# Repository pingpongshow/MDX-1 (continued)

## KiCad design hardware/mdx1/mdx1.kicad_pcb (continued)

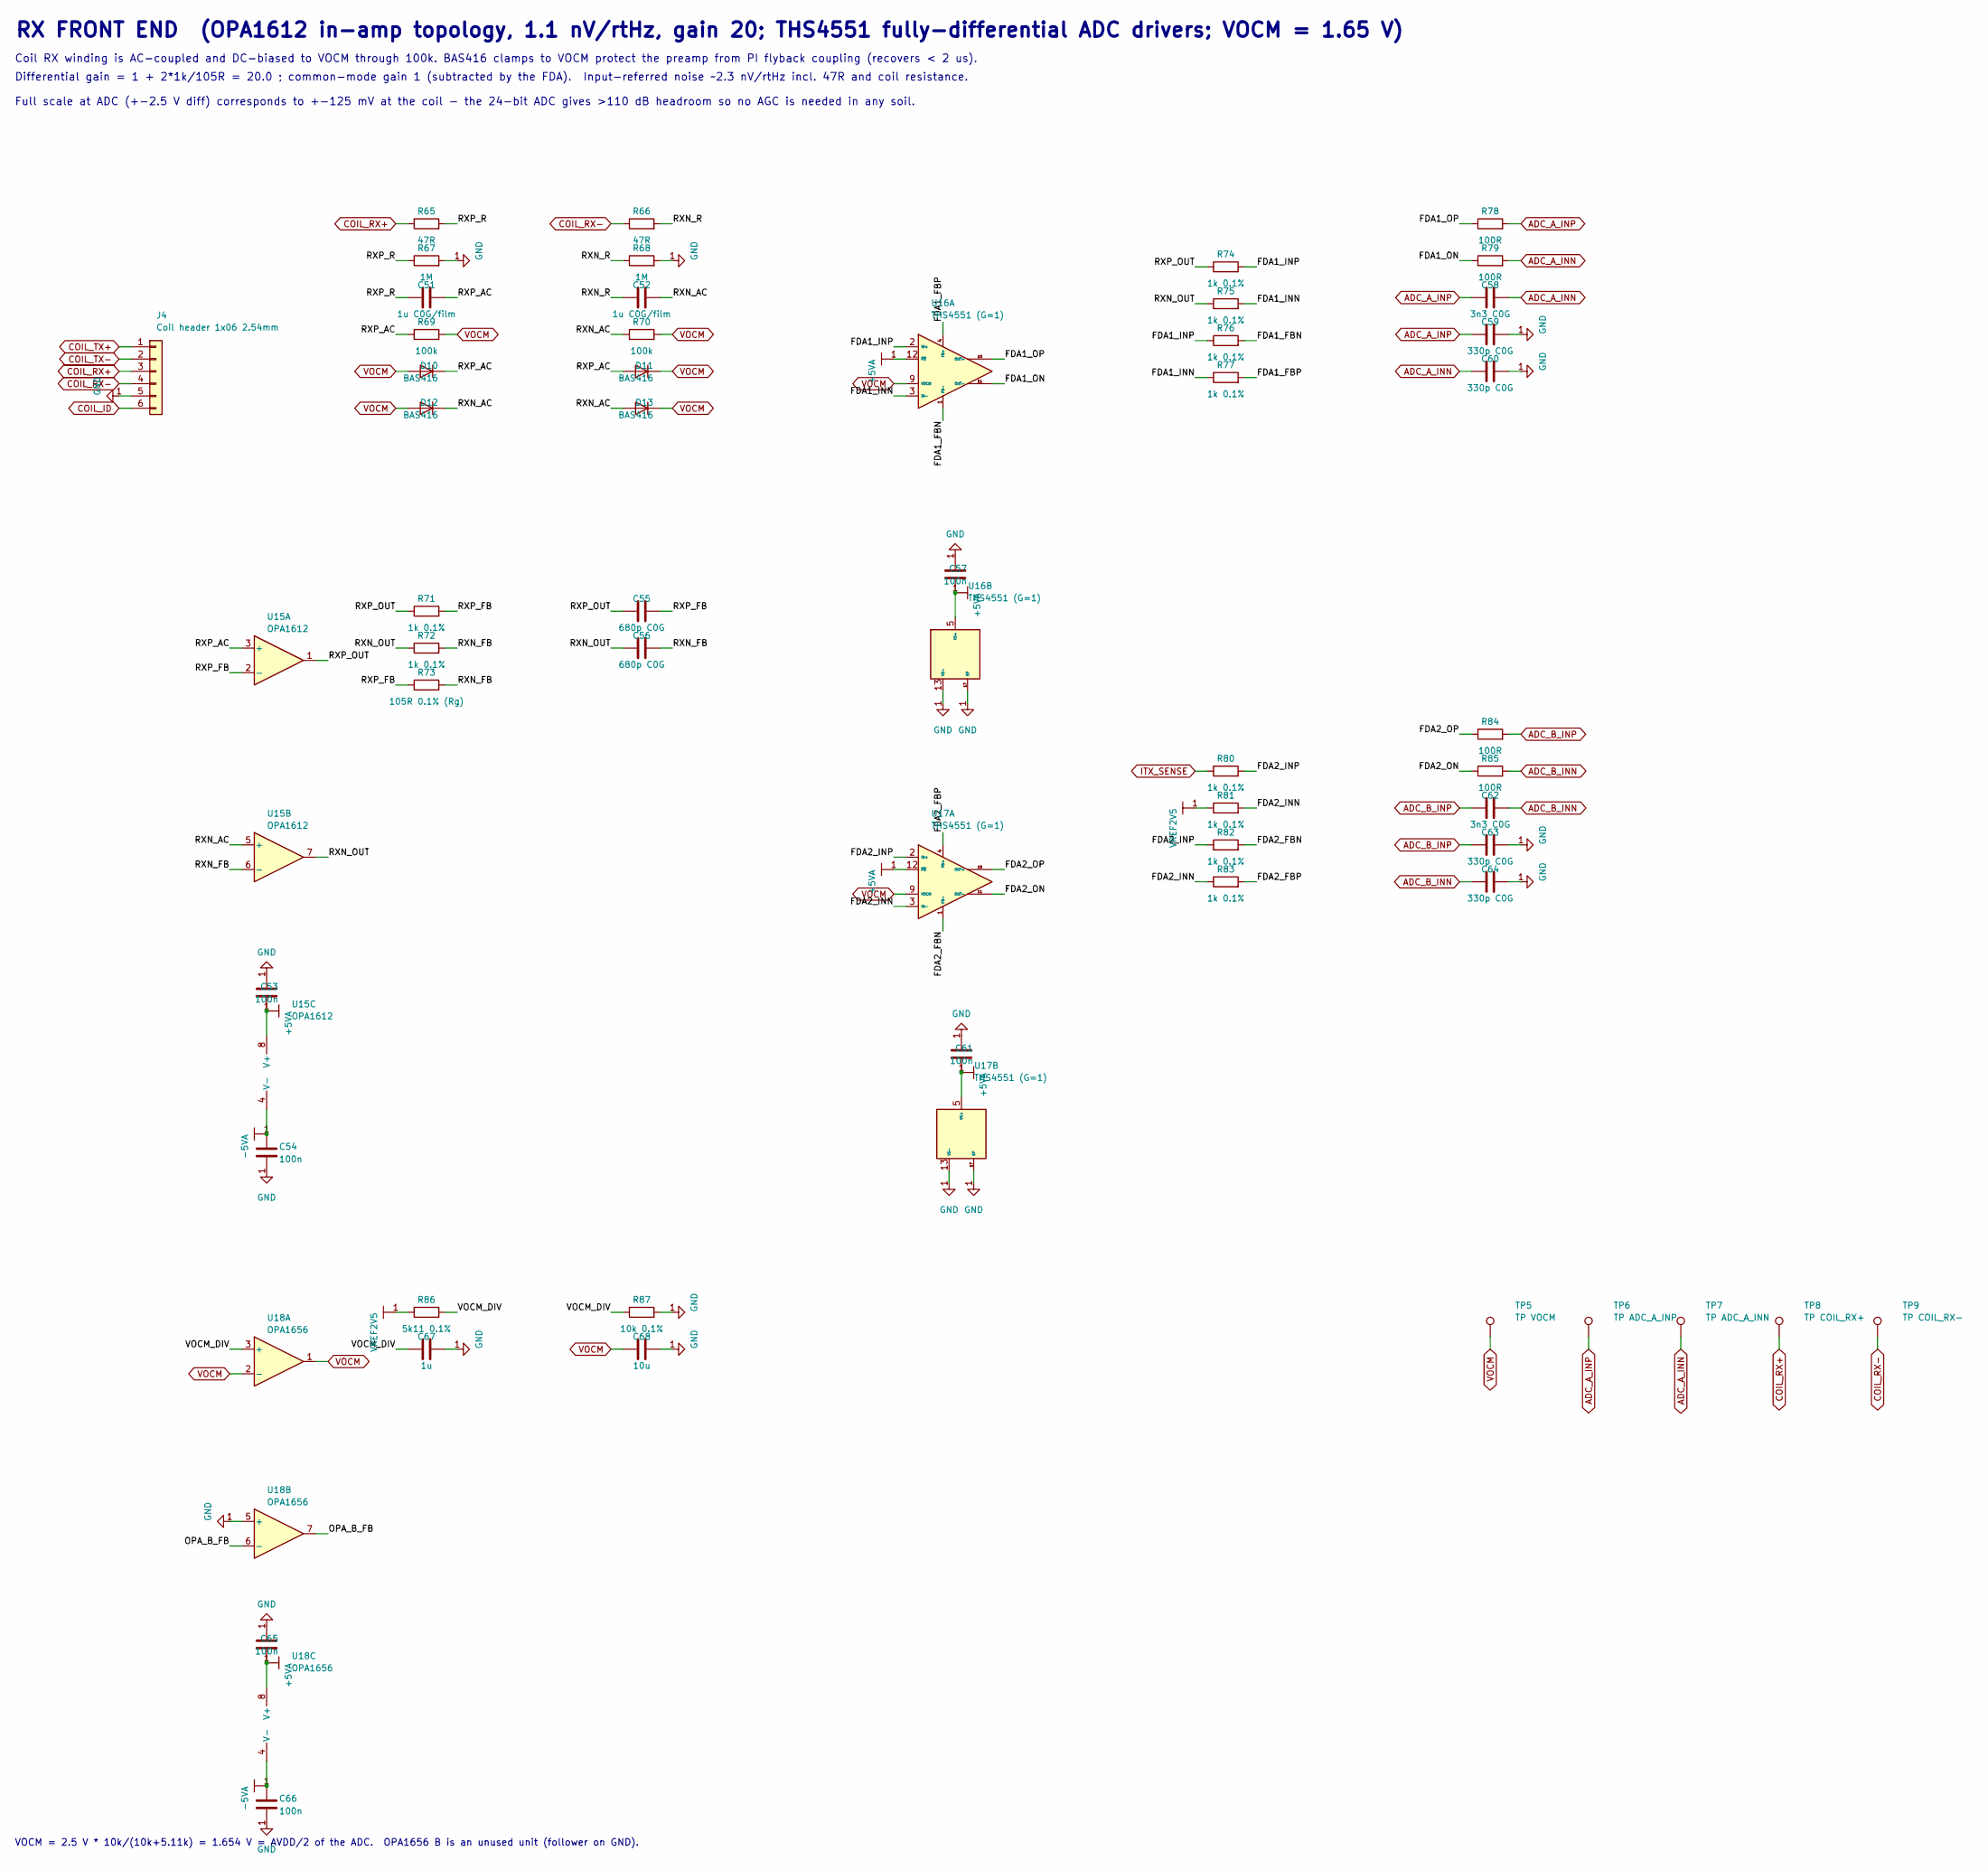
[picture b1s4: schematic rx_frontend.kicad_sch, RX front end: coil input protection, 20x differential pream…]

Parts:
C51, C52: 1u C0G/film; C_1210_3225Metric
C53, C54, C57, C61, C65, C66: 100n; C_0402_1005Metric
C55, C56: 680p C0G; C_0402_1005Metric
C58, C62: 3n3 C0G; C_0402_1005Metric
C59, C60, C63, C64: 330p C0G; C_0402_1005Metric
C67: 1u; C_0402_1005Metric
C68: 10u; C_0805_2012Metric
D10, D11, D12, D13: BAS416; SOT-23
J4: Coil header 1x06 2.54mm; PinHeader_1x06_P2.54mm_Vertical
R65, R66: 47R; R_0402_1005Metric
R67, R68: 1M; R_0402_1005Metric
R69, R70: 100k; R_0402_1005Metric
R71, R72, R74, R75, R76, R77, R80, R81, R82, R83: 1k 0.1%; R_0402_1005Metric
R73: 105R 0.1% (Rg); R_0402_1005Metric
R78, R79, R84, R85: 100R; R_0402_1005Metric
R86: 5k11 0.1%; R_0402_1005Metric
R87: 10k 0.1%; R_0402_1005Metric
TP5: TP VOCM; TestPoint_Pad_D1.5mm
TP6: TP ADC_A_INP; TestPoint_Pad_D1.5mm
TP7: TP ADC_A_INN; TestPoint_Pad_D1.5mm
TP8: TP COIL_RX+; TestPoint_Pad_D1.5mm
TP9: TP COIL_RX-; TestPoint_Pad_D1.5mm
U15: OPA1612
U16: THS4551 (G=1); VQFN-16-1EP_3x3mm_P0.5mm_EP1.68x1.68mm
U17: THS4551 (G=1)
U18: OPA1656

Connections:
+5VA: C53.1, C57.1, C61.1, C65.1, U15.8 (V+), U16.5 (VS+), U16.6 (VS+), U16.7 (VS+), U16.8 (VS+), U16.12 (~PD), U17.5 (VS+), U17.6 (VS+), U17.7 (VS+), U17.8 (VS+), U17.12 (~PD), U18.8 (V+); also elsewhere on the board
-5VA: C54.1, C66.1, U15.4 (V-), U18.4 (V-); also elsewhere on the board
/RX front end: coil input protection, 20x differential preamp, ADC drivers/FDA1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: R76.2, U16.1 (FB-)
/RX front end: coil input protection, 20x differential preamp, ADC drivers/FDA1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: R77.2, U16.4 (FB+)
/RX front end: coil input protection, 20x differential preamp, ADC drivers/FDA1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: R75.2, R77.1, U16.3 (IN-)
/RX front end: coil input protection, 20x differential preamp, ADC drivers/FDA1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: R74.2, R76.1, U16.2 (IN+)
/RX front end: coil input protection, 20x differential preamp, ADC drivers/FDA1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: R79.1, U16.11 (OUT-)
/RX front end: coil input protection, 20x differential preamp, ADC drivers/FDA1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: R78.1, U16.10 (OUT+)
/RX front end: coil input protection, 20x differential preamp, ADC drivers/FDA2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: R82.2, U17.1 (FB-)
/RX front end: coil input protection, 20x differential preamp, ADC drivers/FDA2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: R83.2, U17.4 (FB+)
/RX front end: coil input protection, 20x differential preamp, ADC drivers/FDA2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: R81.2, R83.1, U17.3 (IN-)
/RX front end: coil input protection, 20x differential preamp, ADC drivers/FDA2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: R80.2, R82.1, U17.2 (IN+)
/RX front end: coil input protection, 20x differential preamp, ADC drivers/FDA2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: R85.1, U17.11 (OUT-)
/RX front end: coil input protection, 20x differential preamp, ADC drivers/FDA2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: R84.1, U17.10 (OUT+)
/RX front end: coil input protection, 20x differential preamp, ADC drivers/OPA_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: U18.6 (-), U18.7
/RX front end: coil input protection, 20x differential preamp, ADC drivers/RXN_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: C52.2, D12.1 (K), D13.2 (A), R70.1, U15.5 (+)
/RX front end: coil input protection, 20x differential preamp, ADC drivers/RXN_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: C56.2, R72.2, R73.2, U15.6 (-)
/RX front end: coil input protection, 20x differential preamp, ADC drivers/RXN_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: C56.1, R72.1, R75.1, U15.7
/RX front end: coil input protection, 20x differential preamp, ADC drivers/RXN_R: C52.1, R66.2, R68.1
/RX front end: coil input protection, 20x differential preamp, ADC drivers/RXP_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: C51.2, D10.1 (K), D11.2 (A), R69.1, U15.3 (+)
/RX front end: coil input protection, 20x differential preamp, ADC drivers/RXP_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: C55.2, R71.2, R73.1, U15.2 (-)
/RX front end: coil input protection, 20x differential preamp, ADC drivers/RXP_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: C55.1, R71.1, R74.1, U15.1
/RX front end: coil input protection, 20x differential preamp, ADC drivers/RXP_R: C51.1, R65.2, R67.1
/RX front end: coil input protection, 20x differential preamp, ADC drivers/VOCM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: C67.1, R86.2, R87.1, U18.3 (+)
ADC_A_INN: C58.2, C60.1, R79.2, TP7.1 (1_1); also elsewhere on the board
ADC_A_INP: C58.1, C59.1, R78.2, TP6.1 (1_1); also elsewhere on the board
ADC_B_INN: C62.2, C64.1, R85.2; also elsewhere on the board
ADC_B_INP: C62.1, C63.1, R84.2; also elsewhere on the board
COIL_ID: J4.6; also elsewhere on the board
COIL_RX+: J4.3, R65.1, TP8.1 (1_1)
COIL_RX-: J4.4, R66.1, TP9.1 (1_1)
COIL_TX+: J4.1; also elsewhere on the board
COIL_TX-: J4.2; also elsewhere on the board
ITX_SENSE: R80.1; also elsewhere on the board
VOCM: C68.1, D10.2 (A), D11.1 (K), D12.2 (A), D13.1 (K), R69.2, R70.2, TP5.1 (1_1), U16.9 (VOCM), U17.9 (VOCM), U18.1, U18.2 (-)
VREF2V5: R81.1, R86.1; also elsewhere on the board

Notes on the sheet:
Coil RX winding is AC-coupled and DC-biased to VOCM through 100k. BAS416 clamps to VOCM protect the preamp from PI flyback coupling (recovers < 2 us).
VOCM = 2.5 V * 10k/(10k+5.11k) = 1.654 V = AVDD/2 of the ADC. OPA1656 B is an unused unit (follower on GND).
Full scale at ADC (+-2.5 V diff) corresponds to +-125 mV at the coil - the 24-bit ADC gives >110 dB headroom so no AGC is needed in any soil.
RX FRONT END (OPA1612 in-amp topology, 1.1 nV/rtHz, gain 20; THS4551 fully-differential ADC drivers; VOCM = 1.65 V)
Differential gain = 1 + 2*1k/105R = 20.0 ; common-mode gain 1 (subtracted by the FDA). Input-referred noise ~2.3 nV/rtHz incl. 47R and coil resistance.

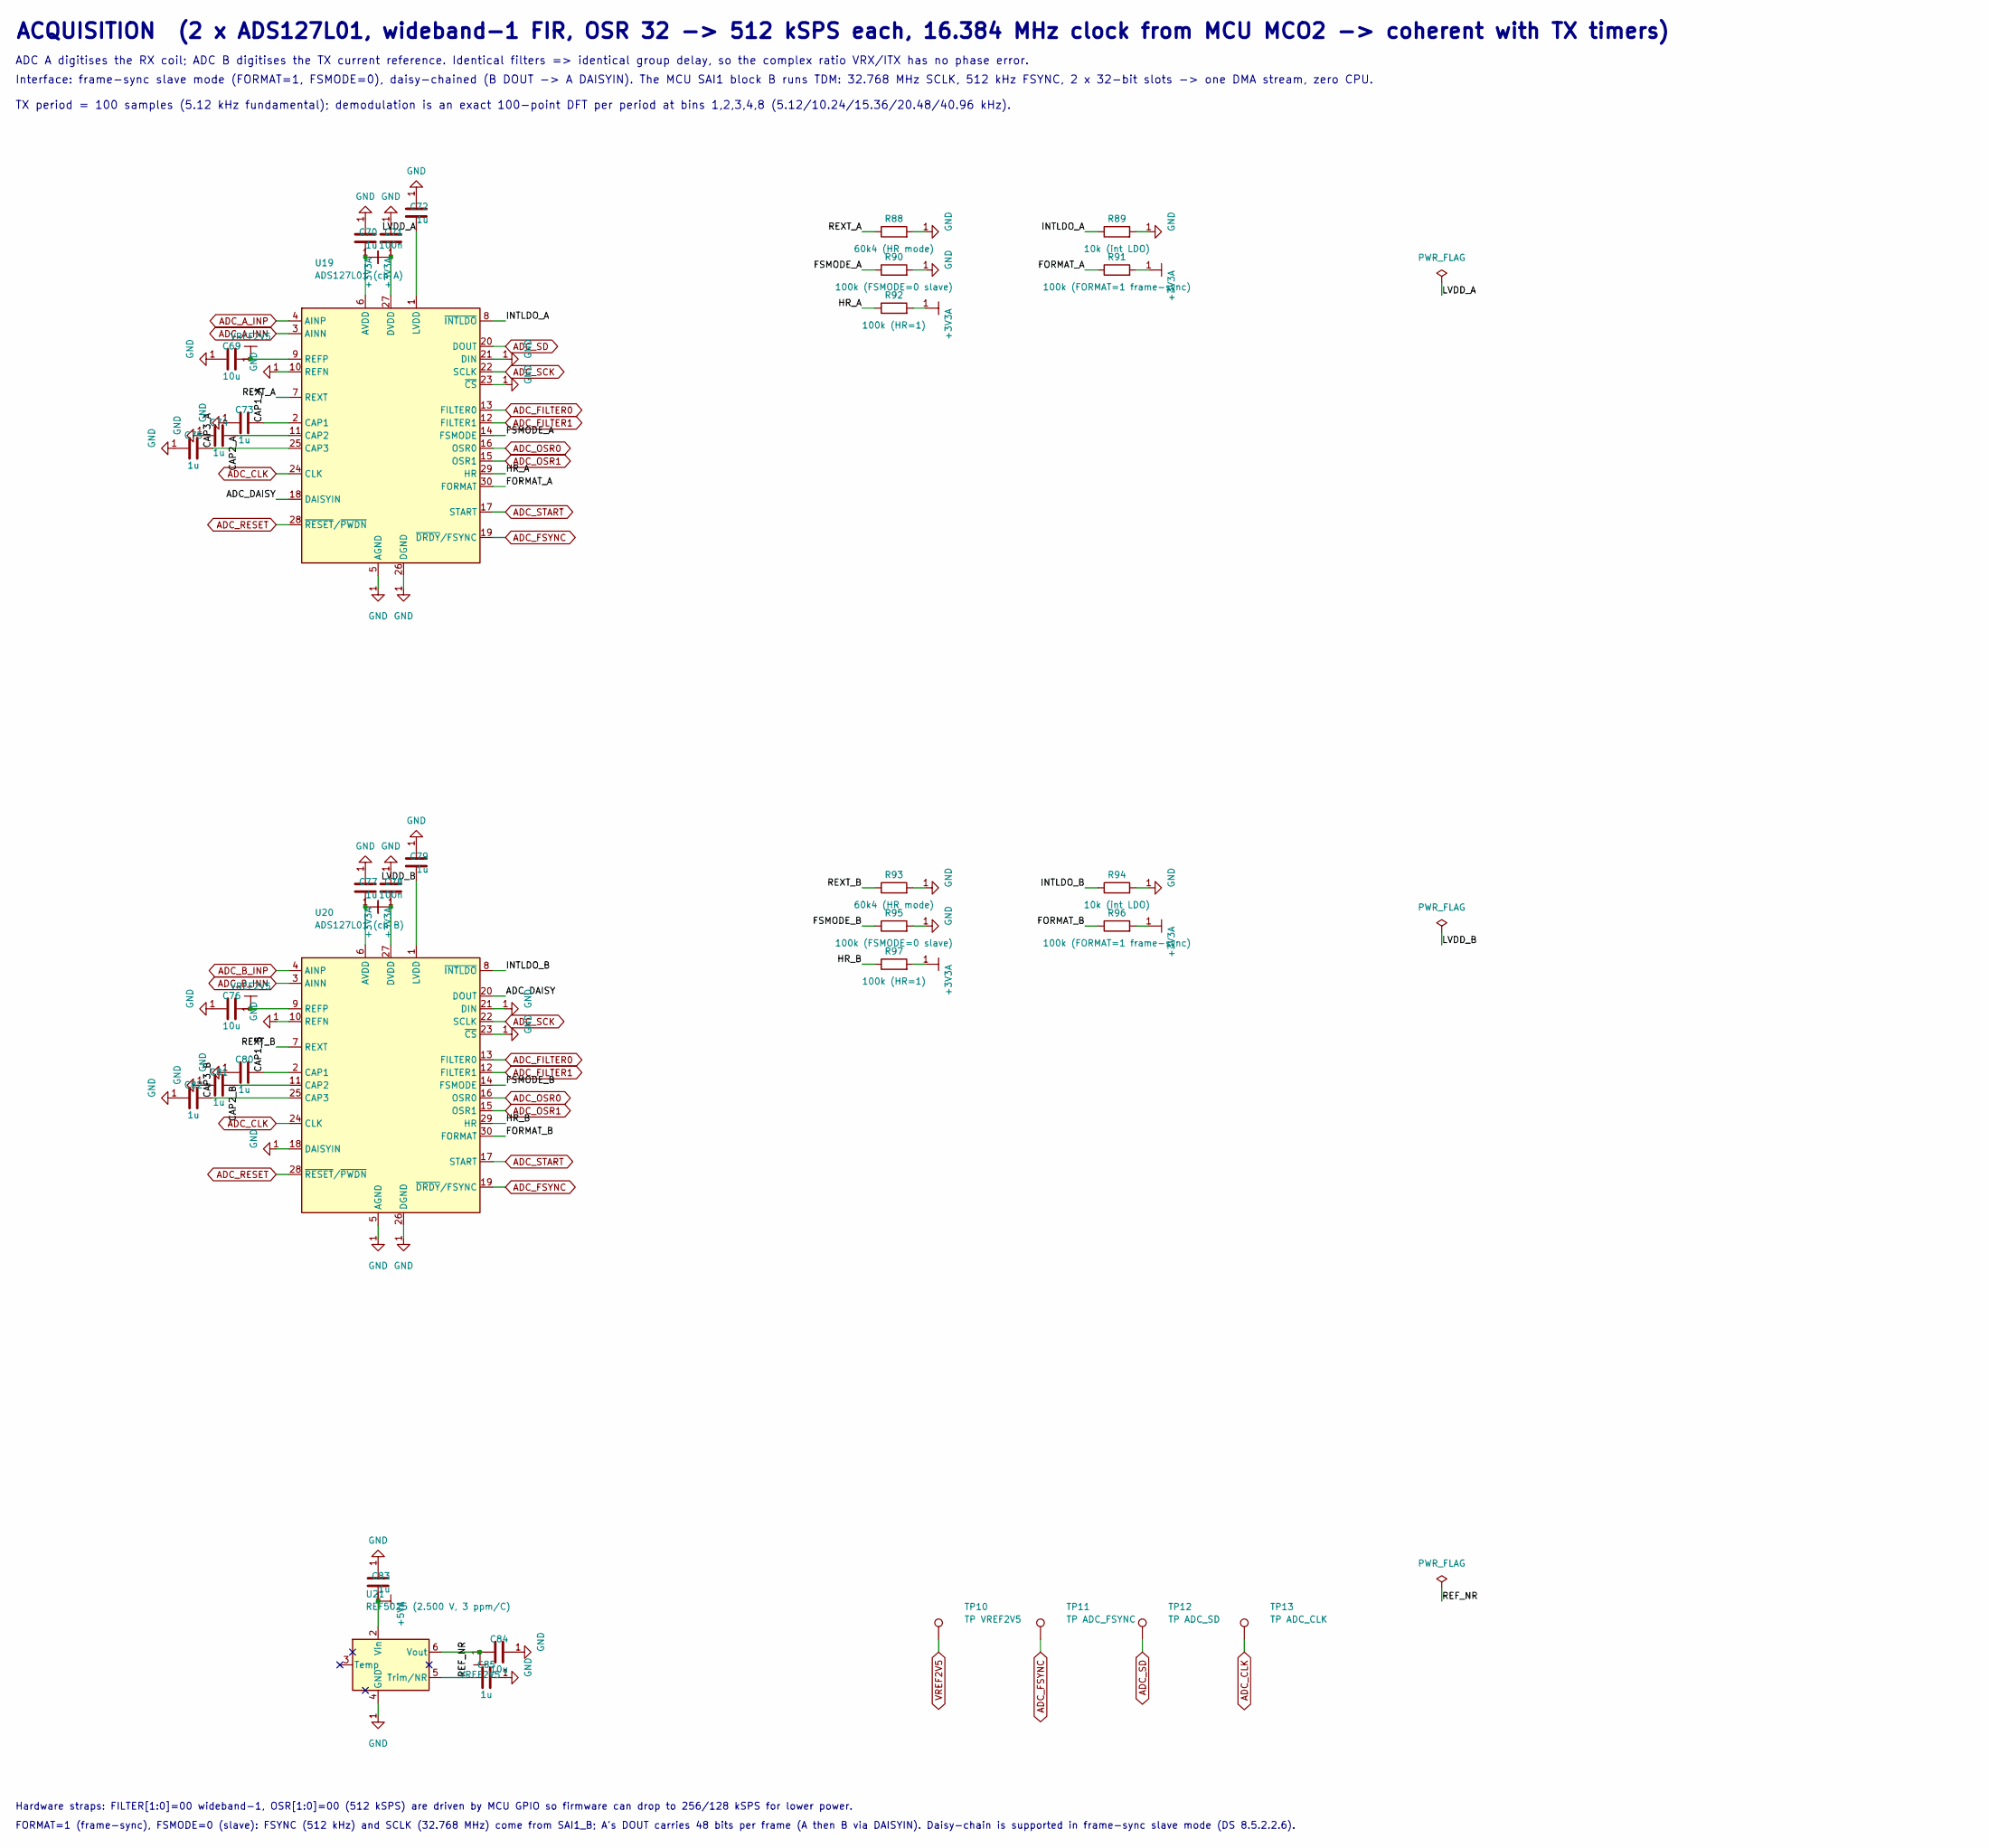
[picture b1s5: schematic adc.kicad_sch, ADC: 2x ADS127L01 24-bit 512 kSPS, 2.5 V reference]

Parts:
C69, C76, C84: 10u; C_0805_2012Metric
C70, C72, C73, C74, C75, C77, C79, C80, C81, C82, C83, C85: 1u; C_0603_1608Metric
C71, C78: 100n; C_0402_1005Metric
R88, R93: 60k4 (HR mode); R_0402_1005Metric
R89, R94: 10k (int LDO); R_0402_1005Metric
R90, R95: 100k (FSMODE=0 slave); R_0402_1005Metric
R91, R96: 100k (FORMAT=1 frame-sync); R_0402_1005Metric
R92, R97: 100k (HR=1); R_0402_1005Metric
TP10: TP VREF2V5; TestPoint_Pad_D1.5mm
TP11: TP ADC_FSYNC; TestPoint_Pad_D1.5mm
TP12: TP ADC_SD; TestPoint_Pad_D1.5mm
TP13: TP ADC_CLK; TestPoint_Pad_D1.5mm
U19: ADS127L01 (ch A); TQFP-32_5x5mm_P0.5mm
U20: ADS127L01 (ch B); TQFP-32_5x5mm_P0.5mm
U21: REF5025 (2.500 V, 3 ppm/C); SOIC-8_3.9x4.9mm_P1.27mm

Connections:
+3V3A: C70.1, C71.1, C77.1, C78.1, R91.2, R92.2, R96.2, R97.2, U19.6 (AVDD), U19.27 (DVDD), U19.32 (AVDD), U20.6 (AVDD), U20.27 (DVDD), U20.32 (AVDD); also elsewhere on the board
+5VA: C83.1, U21.2 (Vin); also elsewhere on the board
/ADC: 2x ADS127L01 24-bit 512 kSPS, 2.5 V reference/ADC_DAISY: U19.18 (DAISYIN), U20.20 (DOUT)
/ADC: 2x ADS127L01 24-bit 512 kSPS, 2.5 V reference/CAP1_A: C73.1, U19.2 (CAP1)
/ADC: 2x ADS127L01 24-bit 512 kSPS, 2.5 V reference/CAP1_B: C80.1, U20.2 (CAP1)
/ADC: 2x ADS127L01 24-bit 512 kSPS, 2.5 V reference/CAP2_A: C74.1, U19.11 (CAP2)
/ADC: 2x ADS127L01 24-bit 512 kSPS, 2.5 V reference/CAP2_B: C81.1, U20.11 (CAP2)
/ADC: 2x ADS127L01 24-bit 512 kSPS, 2.5 V reference/CAP3_A: C75.1, U19.25 (CAP3)
/ADC: 2x ADS127L01 24-bit 512 kSPS, 2.5 V reference/CAP3_B: C82.1, U20.25 (CAP3)
/ADC: 2x ADS127L01 24-bit 512 kSPS, 2.5 V reference/FORMAT_A: R91.1, U19.30 (FORMAT)
/ADC: 2x ADS127L01 24-bit 512 kSPS, 2.5 V reference/FORMAT_B: R96.1, U20.30 (FORMAT)
/ADC: 2x ADS127L01 24-bit 512 kSPS, 2.5 V reference/FSMODE_A: R90.1, U19.14 (FSMODE)
/ADC: 2x ADS127L01 24-bit 512 kSPS, 2.5 V reference/FSMODE_B: R95.1, U20.14 (FSMODE)
/ADC: 2x ADS127L01 24-bit 512 kSPS, 2.5 V reference/HR_A: R92.1, U19.29 (HR)
/ADC: 2x ADS127L01 24-bit 512 kSPS, 2.5 V reference/HR_B: R97.1, U20.29 (HR)
/ADC: 2x ADS127L01 24-bit 512 kSPS, 2.5 V reference/INTLDO_A: R89.1, U19.8 (~INTLDO)
/ADC: 2x ADS127L01 24-bit 512 kSPS, 2.5 V reference/INTLDO_B: R94.1, U20.8 (~INTLDO)
/ADC: 2x ADS127L01 24-bit 512 kSPS, 2.5 V reference/LVDD_A: C72.1, U19.1 (LVDD)
/ADC: 2x ADS127L01 24-bit 512 kSPS, 2.5 V reference/LVDD_B: C79.1, U20.1 (LVDD)
/ADC: 2x ADS127L01 24-bit 512 kSPS, 2.5 V reference/REF_NR: C85.1, U21.5 (Trim/NR)
/ADC: 2x ADS127L01 24-bit 512 kSPS, 2.5 V reference/REXT_A: R88.1, U19.7 (REXT)
/ADC: 2x ADS127L01 24-bit 512 kSPS, 2.5 V reference/REXT_B: R93.1, U20.7 (REXT)
ADC_A_INN: U19.3 (AINN); also elsewhere on the board
ADC_A_INP: U19.4 (AINP); also elsewhere on the board
ADC_B_INN: U20.3 (AINN); also elsewhere on the board
ADC_B_INP: U20.4 (AINP); also elsewhere on the board
ADC_CLK: TP13.1 (1_1), U19.24 (CLK), U20.24 (CLK); also elsewhere on the board
ADC_FILTER0: U19.13 (FILTER0), U20.13 (FILTER0); also elsewhere on the board
ADC_FILTER1: U19.12 (FILTER1), U20.12 (FILTER1); also elsewhere on the board
ADC_FSYNC: TP11.1 (1_1), U19.19 (~DRDY/FSYNC), U20.19 (~DRDY/FSYNC); also elsewhere on the board
ADC_OSR0: U19.16 (OSR0), U20.16 (OSR0); also elsewhere on the board
ADC_OSR1: U19.15 (OSR1), U20.15 (OSR1); also elsewhere on the board
ADC_RESET: U19.28 (~RESET/~PWDN), U20.28 (~RESET/~PWDN); also elsewhere on the board
ADC_SCK: U19.22 (SCLK), U20.22 (SCLK); also elsewhere on the board
ADC_SD: TP12.1 (1_1), U19.20 (DOUT); also elsewhere on the board
ADC_START: U19.17 (START), U20.17 (START); also elsewhere on the board
VREF2V5: C69.1, C76.1, C84.1, TP10.1 (1_1), U19.9 (REFP), U20.9 (REFP), U21.6 (Vout); also elsewhere on the board

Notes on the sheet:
ADC A digitises the RX coil; ADC B digitises the TX current reference. Identical filters => identical group delay, so the complex ratio VRX/ITX has no phase error.
Interface: frame-sync slave mode (FORMAT=1, FSMODE=0), daisy-chained (B DOUT -> A DAISYIN). The MCU SAI1 block B runs TDM: 32.768 MHz SCLK, 512 kHz FSYNC, 2 x 32-bit slots -> one DMA stream, zero CPU.
Hardware straps: FILTER[1:0]=00 wideband-1, OSR[1:0]=00 (512 kSPS) are driven by MCU GPIO so firmware can drop to 256/128 kSPS for lower power.
TX period = 100 samples (5.12 kHz fundamental); demodulation is an exact 100-point DFT per period at bins 1,2,3,4,8 (5.12/10.24/15.36/20.48/40.96 kHz).
ACQUISITION (2 x ADS127L01, wideband-1 FIR, OSR 32 -> 512 kSPS each, 16.384 MHz clock from MCU MCO2 -> coherent with TX timers)
FORMAT=1 (frame-sync), FSMODE=0 (slave): FSYNC (512 kHz) and SCLK (32.768 MHz) come from SAI1_B; A's DOUT carries 48 bits per frame (A then B via DAISYIN). Daisy-chain is supported in frame-sync slave mode (DS 8.5.2.2.6).

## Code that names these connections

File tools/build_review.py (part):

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 ("LT3757 ×2", "SENSE", "20 mΩ; 50 mΩ", "VSENSE(MAX) 108 mV → 5.4 A and 2.2 A switch peak", "OK for 1.5 W and 2 W converters", "ok"),
 ("LT3757 ×2", "SS, VC, INTVCC, SYNC", "100 n/220 n; 22 k + 4.7 n/10 n; 4.7 µF; GND", "Typical values per datasheet applications; SYNC to GND if unused", "OK", "ok"),
 ("LT3757 ×2", "SHDN/UVLO", "MCU GPIO 3.3 V", "Rising threshold 1.22 V", "OK", "ok"),
 ("UCC27714 ×2", "EN/NC (pin 4)", "MCU DRV_EN", "Low disables both outputs; high or floating enables; VENH 2.3 V typ", "OK with 3.3 V logic", "ok"),
 ("UCC27714 ×2", "HB–HS bootstrap", "220 nF, US1D 200 V diode", "≈ 10× gate capacitance", "OK (Qg 30 nC → Ciss ≈ 3 nF)", "ok"),
 ("INA241A2", "REF1 = REF2", "VREF2V5", "0 V to VS; REF1 = REF2 = VREF gives bidirectional output around VREF", "OK: 2.5 V ± 0.4 V/A", "ok"),
 ("INA241A2", "IN± common mode", "0 to 100 V (VBRIDGE)", "−5 V to 110 V", "OK", "ok"),
 ("TLV3501 ×2", "SHDN", "GND", "Enabled when more than 1.7 V below V+; disabled within 0.9 V of V+", "OK", "ok"),
 ("OPA1612", "supply", "±5 V", "±2.25 V to ±18 V", "OK", "ok"),
 ("THS4551 ×2", "PD, VOCM, FB±", "PD → VS+; VOCM 1.65 V; FB± as feedback nodes", "PD active low; single supply 2.7–5.4 V; FB± are output feedback pins", "OK", "ok"),
 ("BQ24075", "EN1 / EN2", "EN1 = 0, EN2 = VBUS", "EN2 = 1, EN1 = 0: input limit set by ILIM resistor (Table 7-2)", "OK", "ok"),
 ("BQ24075", "ILIM / ISET / TMR / TS", "1.1 kΩ / 887 Ω / 47 kΩ / 10 kΩ", "ILIM 1.1–8 kΩ; ISET 590–8900 Ω; TMR 18–72 kΩ; TS 10 kΩ if no NTC", "OK (1.4 A in, 1.0 A charge)", "ok"),
 ("BQ24075", "SYSOFF, CE", "GND, GND", "SYSOFF low = system connected; CE low = charging enabled", "OK", "ok"),
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 ("TPA6132A2", "G0 / G1, EN", "+3V3 / GND; MCU HP_EN", "G0 ≥ 1.3 V, G1 ≤ 0.5 V → 0 dB; EN high = active", "OK", "ok"),
 ("TPA6132A2", "CPP–CPN, HPVSS", "1 µF, 1 µF", "1 µF flying cap, 1 µF at HPVSS", "OK", "ok"),
 ("MAX-M10S", "VIO_SEL", "open", "Open = 3.3 V I/O; GND = 1.8 V", "OK", "ok"),
 ("MAX-M10S", "SAFEBOOT_N / TIMEPULSE", "open / MCU input", "Shared through 1 kΩ; must not be low at start-up", "OK (PD0 is an input with no pull-down)", "ok"),
 ("MAX-M10S", "RESET_N, EXTINT, V_BCKP", "MCU GPIO, open, +3V3", "Active low ≥ 1 ms; leave EXTINT open; V_BCKP ≤ 3.6 V", "OK", "ok"),
 ("LSM6DSO32", "CS, SDO/SA0", "+3V3; 0 Ω to GND", "CS = 1 enables I2C; SA0 = 0 → address 0x6A", "OK (drop-in for LSM6DSM; FS_XL encoding differs, handled in firmware)", "ok"),
 ("PAM8302A", "~SD", "MCU SPK_SD", "Low = shutdown", "OK (firmware drives high to enable)", "ok"),
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 ("BQ27441-G1", "BAT", "no bypass", "0.1 µF at BAT recommended", "100 nF added", "fixed"),
 ("PAM8302A", "IN± coupling, VDD bypass", "1 µF, 100 nF", "0.1 to 0.22 µF input coupling; 1 µF at VDD", "220 nF and 1 µF", "fixed"),
 ("Bring-up", "test points", "none", "-", "15 test pads: ITX, fault, coil TX/RX, VOCM, ADC inputs, reference, SAI lines, SWO, NRST", "fixed"),
 ("Rev A4: STM32H743 VDD", "14 VDD pins", "one capacitor per pin (11)", "Owner's call: VDD pins on the +3V3 plane, one bulk + one HF capacitor", "4.7 µF + 100 nF at the package; VCAP1/2 keep their 2.2 µF (core-regulator outputs, required by ST); VDDA keeps bead + 1 µF / 100 nF", "fixed"),
 ("Rev A4: keypad", "8 keys + power", "MENU BACK UP DOWN LEFT RIGHT PINPOINT GB POWER", "Owner's call: simplify", "MENU UP DOWN LEFT RIGHT + PINPOINT trigger + POWER; BACK = MENU held 0.8 s, ground grab = PINPOINT held 1.5 s; PG15 and PB4 freed", "fixed"),
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]
PINS = [
 ("PE9 / PE8", "TIM1_CH1 / CH1N", "AF1", "Table 10 p.94", "bridge A high / low gates"), ("PE11 / PE10", "TIM1_CH2 / CH2N", "AF1", "Table 10 p.94", "bridge B gates"),
 ("PE15", "TIM1_BKIN", "AF1", "Table 10 p.94", "over-current break"), ("PC9", "MCO2", "AF0", "Table 10 p.93", "16.384 MHz to both ADCs; PC9 is also SDMMC1_D1, so the SD card runs 1-bit"),
 ("PF8 / PF9 / PF6", "SAI1_SCK_B / FS_B / SD_B", "AF6", "Table 10 p.95", "ADC frame-sync interface"), ("PE2 / PE4 / PE5 / PE6", "SAI1_MCLK_A / FS_A / SCK_A / SD_A", "AF6", "Table 10 p.94", "I2S to the Bluetooth module"),
 ("PE12 / PE14", "SPI4_SCK / MOSI", "AF5", "Table 10 p.94", "memory LCD"), ("PD15", "TIM4_CH4", "AF2", "Table 10 p.93", "front-light PWM"),
 ("PB8 / PB9", "I2C1_SCL / SDA", "AF4", "Table 10 p.91", "fuel gauge, IMU"), ("PC10 / PC11", "UART4_TX / RX", "AF8", "Table 10 p.93", "GNSS"),
 ("PA9 / PA10", "USART1_TX / RX", "AF7", "Table 9 p.80", "Bluetooth module; PA9 also carries OTG_FS_VBUS, so USB VBUS sensing is disabled in firmware"),
 ("PA11 / PA12", "OTG_FS_DM / DP", "AF10", "Table 9 p.80", "USB-C"), ("PC8 / PC12 / PD2", "SDMMC1_D0 / CK / CMD", "AF12", "Table 9 p.80–83", "microSD, 1-bit"),
 ("PA0 / PA1 / PA2 / PA3", "ADC1_INP16 / INP17 / ADC12_INP14 / INP15", "analog", "Table 9 p.68", "VTX, VBRIDGE, VBAT, VBUS monitors"), ("PA4 / PA5", "DAC1_OUT1 / OUT2", "analog", "Table 9 p.68–69", "VTX set-point, audio"),
 ("PA13 / PA14 / PB3", "SWDIO / SWCLK / TRACESWO", "AF0", "Table 9/10", "debug"), ("PC13", "WKUP4 (RTC_TS)", "-", "Table 9 p.66", "power key; HAL constant corrected to PWR_WAKEUP_PIN4"),
 ("PH0 / PH1, PC14 / PC15", "OSC_IN / OUT, OSC32_IN / OUT", "-", "Table 9", "crystals"), ("PG2–PG6, PG9–PG15, PB4, PF0–PF5, PF10, PD0–PD14 (used ones)", "GPIO", "-", "-", "enables, keys, straps, status inputs; PB4 is NJTRST at reset, fine as an input key"),
]
rows = bom["rows"]; off = bom["offboard"]
tot1, tot100 = bom["total1"], bom["total100"]
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
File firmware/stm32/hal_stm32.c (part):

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
void hal_tx_enable(int on)
{
    HAL_GPIO_WritePin(GPIOG, GPIO_PIN_2, on ? GPIO_PIN_SET : GPIO_PIN_RESET);      /* DRV_EN */
    if (on) { __HAL_TIM_MOE_ENABLE(&htim1); HAL_TIM_PWM_Start(&htim1, TIM_CHANNEL_1); HAL_TIMEx_PWMN_Start(&htim1, TIM_CHANNEL_1); HAL_TIM_PWM_Start(&htim1, TIM_CHANNEL_2); HAL_TIMEx_PWMN_Start(&htim1, TIM_CHANNEL_2); }
    else { __HAL_TIM_MOE_DISABLE(&htim1); }
}
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    /* VTX = 29.8 V - 6.65 * VDAC  (feedback injection, see power sheet) */
    float vdac = (29.8f - volts) / 6.65f; if (vdac < 0) vdac = 0; if (vdac > 3.25f) vdac = 3.25f;
    HAL_DAC_SetValue(&hdac, DAC_CHANNEL_1, DAC_ALIGN_12B_R, (uint32_t)(vdac / 3.3f * 4095.0f));
    HAL_GPIO_WritePin(GPIOG, GPIO_PIN_4, GPIO_PIN_SET);                              /* VTX_EN */
}

int hal_tx_pi_busy(void) { return pi_mode; }
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    uint32_t v = HAL_ADC_GetValue(&hadc1); HAL_ADC_Stop(&hadc1);
    return (float)v * 3.3f / 65535.0f;
}
float hal_tx_rail_v(void)     { return adc1_read(ADC_CHANNEL_16) * (442.0f + 47.0f) / 47.0f; }     /* PA0, 442k/47k + 10k series */
float hal_bridge_rail_v(void) { return adc1_read(ADC_CHANNEL_17) * (1000.0f + 22.0f) / 22.0f; }    /* PA1, 1M/22k */
int  hal_tx_fault(void)       { return (htim1.Instance->SR & TIM_SR_BIF) != 0; }
void hal_tx_clear_fault(void) { htim1.Instance->SR &= ~TIM_SR_BIF; __HAL_TIM_MOE_ENABLE(&htim1); }

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}
void hal_lcd_frontlight(int pct) { __HAL_TIM_SET_COMPARE(&htim4, TIM_CHANNEL_4, (uint32_t)(pct * 10)); }

int hal_ui_present(void) { return (GPIOG->IDR & GPIO_PIN_15) == 0; }        /* UI_DET: UI board grounds link pin 8 */
void hal_status_led(int on) { HAL_GPIO_WritePin(GPIOB, GPIO_PIN_0, on ? GPIO_PIN_RESET : GPIO_PIN_SET); }   /* LED_STAT, active low */
uint32_t hal_keys(void)
{
    uint32_t k = 0; uint16_t g = GPIOG->IDR;
    if (!(g & GPIO_PIN_9))  k |= KEY_MENU;  if (!(g & GPIO_PIN_10)) k |= KEY_UP;    if (!(g & GPIO_PIN_11)) k |= KEY_DOWN;
    if (!(g & GPIO_PIN_12)) k |= KEY_LEFT;  if (!(g & GPIO_PIN_13)) k |= KEY_RIGHT; if (!(g & GPIO_PIN_14)) k |= KEY_PINPOINT;
    if (!(GPIOC->IDR & GPIO_PIN_13)) k |= KEY_POWER;   /* BACK and ground grab are long presses, synthesised in ui_update() */
    return k;
}
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int hal_headphone_present(void) { return HAL_GPIO_ReadPin(GPIOD, GPIO_PIN_6) == GPIO_PIN_SET; }

/* ---- optional low-latency wireless audio (nRF52840 daughterboard on J14) ------------
 * Control link = USART3 (PD8/PD9); NRF_RESET = PG0 (open-drain), NRF_STATUS = PG1 (input).
 * The nRF receives the shared I2S stream (SAI1_A: PE4/PE5/PE6) and transmits it to a puck.
 * The command bytes here are PLACEHOLDERS - match them to your nRF puck-link firmware. */
static int s_ll_enabled = 0, s_ll_present = -1;
static void ll_tx(uint8_t cmd) { HAL_UART_Transmit(&huart3, &cmd, 1, 5); }
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void hal_ll_audio_pair(void) { ll_tx(0xA3 /* PAIR */); }
int  hal_ll_audio_linked(void) { return HAL_GPIO_ReadPin(GPIOG, GPIO_PIN_1) == GPIO_PIN_SET; }

/* ---- expansion header (I2C4 / SPI2 / UART5 / GPIO PE13,PA15) ---- */
void hal_exp_spi_cs(int level) { HAL_GPIO_WritePin(GPIOG, GPIO_PIN_8, level ? GPIO_PIN_SET : GPIO_PIN_RESET); }
int hal_exp_spi(const uint8_t *tx, uint8_t *rx, int n)
{
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}
float hal_battery_v(void) { uint8_t d[2]; if (!i2c_rd(0x55, 0x04, d, 2)) return adc1_read(ADC_CHANNEL_14) * 2.0f; return (d[0] | d[1] << 8) * 1e-3f; }
int  hal_battery_pct(void) { uint8_t d[2]; if (!i2c_rd(0x55, 0x1C, d, 2)) return 50; return d[0] | d[1] << 8; }
int  hal_charging(void)    { return HAL_GPIO_ReadPin(GPIOF, GPIO_PIN_4) == GPIO_PIN_RESET; }   /* CHG_n low = charging */
float hal_rail_v(int r)
{
    switch (r) { case 0: return hal_battery_v(); case 1: return 3.3f; case 2: return 5.0f; case 3: return -5.0f; case 4: return 12.0f; case 5: return hal_tx_rail_v(); default: return hal_bridge_rail_v(); }
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}
int hal_gnss_read(gnss_fix_t *fix) { *fix = g_fix; return 1; }

/* ------------------------------------------------------------------ 1-Wire coil EEPROM (DS2431) on PB5 */
static void ow_delay_us(uint32_t us) { uint32_t t0 = DWT->CYCCNT; while (DWT->CYCCNT - t0 < us * (SystemCoreClock / 1000000u)) ; }
static void ow_low(int low) { GPIOB->BSRR = low ? (GPIO_PIN_5 << 16) : GPIO_PIN_5; }
static int ow_reset(void) { ow_low(1); ow_delay_us(480); ow_low(0); ow_delay_us(70); int p = !(GPIOB->IDR & GPIO_PIN_5); ow_delay_us(410); return p; }
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void SysTick_Handler(void) { HAL_IncTick(); ms_ticks++; static int vc; if (++vc >= 500) { vc = 0; HAL_GPIO_TogglePin(GPIOB, GPIO_PIN_11); vcom ^= 1; } }
uint32_t hal_millis(void) { return ms_ticks; }
void hal_delay_ms(uint32_t ms) { HAL_Delay(ms); }
void hal_power_off(void) { hal_tx_enable(0); hal_analog_enable(0); HAL_PWR_EnableWakeUpPin(PWR_WAKEUP_PIN4_LOW);   /* PC13 = WKUP4 per DS12110 table 9 */ HAL_PWR_EnterSTANDBYMode(); }
void hal_analog_enable(int on) { HAL_GPIO_WritePin(GPIOG, GPIO_PIN_6, on ? GPIO_PIN_SET : GPIO_PIN_RESET); }
void hal_hv_enable(int on) { HAL_GPIO_WritePin(GPIOG, GPIO_PIN_3, on ? GPIO_PIN_SET : GPIO_PIN_RESET); if (!on) { hal_hv_bleed(1); HAL_Delay(600); hal_hv_bleed(0); } }
void hal_hv_bleed(int on) { HAL_GPIO_WritePin(GPIOG, GPIO_PIN_5, on ? GPIO_PIN_SET : GPIO_PIN_RESET); }
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    p.Sai1ClockSelection = RCC_SAI1CLKSOURCE_PLL2; p.AdcClockSelection = RCC_ADCCLKSOURCE_PLL2; p.UsbClockSelection = RCC_USBCLKSOURCE_HSI48;
    p.SdmmcClockSelection = RCC_SDMMCCLKSOURCE_PLL; p.Uart4ClockSelection = RCC_UART4CLKSOURCE_D2PCLK1; p.Usart16ClockSelection = RCC_USART16CLKSOURCE_D2PCLK2; p.I2c123ClockSelection = RCC_I2C123CLKSOURCE_D2PCLK1; p.Spi45ClockSelection = RCC_SPI45CLKSOURCE_D2PCLK1;
    HAL_RCCEx_PeriphCLKConfig(&p);
    HAL_RCC_MCOConfig(RCC_MCO2, RCC_MCO2SOURCE_HSE, RCC_MCODIV_1);       /* PC9 -> ADC CLK 16.384 MHz */
    DWT->CTRL |= DWT_CTRL_CYCCNTENA_Msk; CoreDebug->DEMCR |= CoreDebug_DEMCR_TRCENA_Msk;
}

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    __HAL_RCC_GPIOA_CLK_ENABLE(); __HAL_RCC_GPIOB_CLK_ENABLE(); __HAL_RCC_GPIOC_CLK_ENABLE(); __HAL_RCC_GPIOD_CLK_ENABLE(); __HAL_RCC_GPIOE_CLK_ENABLE(); __HAL_RCC_GPIOF_CLK_ENABLE(); __HAL_RCC_GPIOG_CLK_ENABLE(); __HAL_RCC_GPIOH_CLK_ENABLE();
    GPIO_InitTypeDef g = {0};
    g.Mode = GPIO_MODE_OUTPUT_PP; g.Speed = GPIO_SPEED_FREQ_LOW;
    g.Pin = GPIO_PIN_2 | GPIO_PIN_3 | GPIO_PIN_4 | GPIO_PIN_5 | GPIO_PIN_6; HAL_GPIO_Init(GPIOG, &g);            /* DRV_EN HV_EN VTX_EN HV_BLEED ANA_EN */
    g.Pin = GPIO_PIN_8; HAL_GPIO_Init(GPIOG, &g); GPIOG->BSRR = GPIO_PIN_8;                                        /* EXP SPI2 chip-select (idle high) */
    g.Pin = GPIO_PIN_0 | GPIO_PIN_1 | GPIO_PIN_2 | GPIO_PIN_3; HAL_GPIO_Init(GPIOF, &g);                          /* ADC straps: FILTER 00, OSR 00 */
    g.Pin = GPIO_PIN_11 | GPIO_PIN_12 | GPIO_PIN_14 | GPIO_PIN_1 | GPIO_PIN_3 | GPIO_PIN_5; HAL_GPIO_Init(GPIOD, &g);   /* ADC START RESET, DISP, SPK_SD, HP_EN, GNSS_RST */
    g.Pin = GPIO_PIN_10 | GPIO_PIN_11 | GPIO_PIN_0 | GPIO_PIN_1; HAL_GPIO_Init(GPIOB, &g);                        /* DISP_CS EXTCOM LEDs */
    g.Pin = GPIO_PIN_3 | GPIO_PIN_7; HAL_GPIO_Init(GPIOE, &g);                                                    /* BT_EN BT_RST */
    g.Mode = GPIO_MODE_OUTPUT_OD; g.Pin = GPIO_PIN_5; HAL_GPIO_Init(GPIOB, &g); GPIOB->BSRR = GPIO_PIN_5;           /* 1-Wire */
    g.Pull = GPIO_PULLUP; g.Pin = GPIO_PIN_0; HAL_GPIO_Init(GPIOG, &g); GPIOG->BSRR = GPIO_PIN_0; g.Pull = GPIO_NOPULL;  /* NRF_RESET (OD, released high) */
    g.Mode = GPIO_MODE_INPUT; g.Pull = GPIO_PULLUP;
    g.Pin = GPIO_PIN_9 | GPIO_PIN_10 | GPIO_PIN_11 | GPIO_PIN_12 | GPIO_PIN_13 | GPIO_PIN_14 | GPIO_PIN_15; HAL_GPIO_Init(GPIOG, &g);   /* keys: MENU UP DOWN LEFT RIGHT PINPOINT; PG15 = UI_DET */
    g.Pin = GPIO_PIN_13; HAL_GPIO_Init(GPIOC, &g);                                                                /* POWER (WKUP4) */
    g.Pin = GPIO_PIN_4 | GPIO_PIN_5 | GPIO_PIN_10; HAL_GPIO_Init(GPIOF, &g);                                      /* CHG PGOOD BAT_INT */
    g.Pin = GPIO_PIN_6 | GPIO_PIN_7; HAL_GPIO_Init(GPIOD, &g);                                                    /* HP_DET SD_DET */
    g.Pull = GPIO_PULLDOWN; g.Pin = GPIO_PIN_1; HAL_GPIO_Init(GPIOE, &g);                                          /* BT_WAKE: BM83 P0_0/UART_TX_IND, active high */
    g.Pin = GPIO_PIN_1; HAL_GPIO_Init(GPIOG, &g); g.Pull = GPIO_PULLUP;                                            /* NRF_STATUS (PG1, low = no puck) */
    g.Pin = GPIO_PIN_13; HAL_GPIO_Init(GPIOE, &g);                                                                 /* EXP_GPIO1 (PE13) default input */
    g.Pin = GPIO_PIN_15; HAL_GPIO_Init(GPIOA, &g);                                                                 /* EXP_GPIO2 (PA15) default input */
    /* alternate functions */
    g.Mode = GPIO_MODE_AF_PP; g.Pull = GPIO_NOPULL; g.Speed = GPIO_SPEED_FREQ_VERY_HIGH;
    g.Alternate = GPIO_AF1_TIM1; g.Pin = GPIO_PIN_8 | GPIO_PIN_9 | GPIO_PIN_10 | GPIO_PIN_11 | GPIO_PIN_15; HAL_GPIO_Init(GPIOE, &g);
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
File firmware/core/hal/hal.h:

/* Hardware abstraction layer for the MDX-1 core.
 * Two implementations: sim/hal_sim.c (host, physics simulator) and stm32/hal_stm32.c (target).
 * The core never touches hardware directly; it only calls these functions. */
#ifndef MDX_HAL_H
#define MDX_HAL_H
#include <stdint.h>
#include <stddef.h>
#include "../mdx_config.h"

/* ---- acquisition ------------------------------------------------------------------ */
typedef struct {
    int32_t rx[MDX_MAXM];     /* ADC A codes, one transmit period                     */
    int32_t itx[MDX_MAXM];    /* ADC B codes, same samples                            */
    int     M;                /* samples in this period                               */
    uint32_t t_ms;            /* time stamp of first sample                           */
    uint32_t seq;             /* period counter (detects drops)                       */
} adc_frame_t;

/* PI-mode decay record: samples following one current reversal */
#define MDX_PI_MAX_SAMPLES 128
typedef struct {
    int32_t rx[MDX_PI_MAX_SAMPLES];
    int     n;
    int     polarity;         /* +1 / -1: direction of the reversal that preceded it */
    uint32_t t_ms;
} pi_record_t;

/* Returns 1 and fills *f when a complete period is available, 0 otherwise. Non-blocking. */
int  hal_adc_get_frame(adc_frame_t *f);
int  hal_adc_get_pi_record(pi_record_t *r);
void hal_adc_set_period(int M);           /* reconfigures the DMA frame length            */

/* ---- transmit ------------------------------------------------------------------- */
typedef struct {
    uint16_t ticks[MDX_SLOTS];  /* timer ARR per slot                                 */
    int8_t   level[MDX_SLOTS];  /* -1, 0, +1 bridge state per slot                    */
} tx_table_t;
typedef struct {
    float    rail_v;            /* bridge rail for PI (VBRIDGE), e.g. 100 V           */
    float    current_a;         /* regulated hold current                             */
    uint16_t reversal_us;       /* time allowed for the reversal                      */
    uint16_t hold_us;           /* receive/hold period after each reversal            */
    uint16_t sample_start_us;   /* first sample after reversal                        */
    uint16_t bursts;            /* reversals per PI frame                             */
    uint8_t  continuous;        /* 1 = re-arm forever (pure PI); 0 = one frame, then VLF */
} pi_seq_t;
void hal_tx_set_table(const tx_table_t *t);
void hal_tx_enable(int on);
void hal_tx_set_rail(float volts);         /* VTX set-point via DAC1                        */
void hal_tx_run_pi(const pi_seq_t *seq);   /* switches the bridge to a PI burst, then back  */
int  hal_tx_pi_busy(void);                 /* 1 while a PI burst is still running            */
void hal_tx_pi_stop(void);                 /* ends a burst early and hands back to VLF       */
float hal_tx_rail_v(void);                 /* measured VTX                                  */
float hal_bridge_rail_v(void);             /* measured VBRIDGE                              */
int  hal_tx_fault(void);                   /* TIM1 break latched?                           */
void hal_tx_clear_fault(void);

/* ---- user interface ------------------------------------------------------------- */
#define LCD_W 400
#define LCD_H 240
#define LCD_STRIDE (LCD_W / 8)
void hal_lcd_update(const uint8_t *fb);    /* 1 bpp, 400x240, row-major, MSB left           */
void hal_lcd_frontlight(int pct);
/* physical keys (6-key pad + pinpoint trigger): MENU UP DOWN LEFT RIGHT POWER + PINPOINT.
 * KEY_BACK and KEY_GB are virtual: the UI synthesises BACK from a long press of MENU (0.8 s)
 * and ground grab from PINPOINT held for 1.5 s. hal_keys() never returns them. */
enum { KEY_MENU = 1, KEY_UP = 2, KEY_DOWN = 4, KEY_LEFT = 8, KEY_RIGHT = 16, KEY_PINPOINT = 32, KEY_POWER = 64, KEY_BACK = 128, KEY_GB = 256 };
uint32_t hal_keys(void);                   /* bitmask of pressed keys                       */
int  hal_ui_present(void);                 /* UI_DET pin: UI board plugged in (pin 8 of the link grounded) */
void hal_status_led(int on);               /* main-board status LED (parallel to the UI board one)     */

/* ---- audio ---------------------------------------------------------------------- */
#define AUDIO_FS 32000
typedef void (*audio_fill_cb)(int16_t *buf, int n, void *ctx);
void hal_audio_start(audio_fill_cb cb, void *ctx);
void hal_audio_route(int headphone, int speaker, int bluetooth);
int  hal_headphone_present(void);

/* ---- optional low-latency wireless audio (nRF52840 daughterboard via J14) ----------
 * The BM83 keeps the BLE app link and standard-BT audio; this is an *optional* add-on
 * module that transmits the shared I2S stream to a matching receiver puck at low latency.
 * All calls are safe no-ops when the daughterboard is absent. */
int  hal_ll_audio_present(void);   /* daughterboard fitted / responding on the control link */
void hal_ll_audio_enable(int on);  /* enable/disable the low-latency audio TX link            */
void hal_ll_audio_pair(void);      /* begin pairing to a receiver puck                        */
int  hal_ll_audio_linked(void);    /* 1 = a puck is currently connected (NRF_STATUS)          */

/* ---- expansion header (generic I2C/SPI/UART/GPIO breakout for add-on boards) ----------
 * I2C4 (PF14/PF15), SPI2 (PB13 SCK / PB14 MISO / PB15 MOSI, CS on PG8), UART5 (PB6/PB12),
 * and two GPIO (idx 0 = PE13, 1 = PA15). Behind the HAL so add-on code stays portable. */
int  hal_exp_i2c(uint8_t addr7, const uint8_t *wr, int wn, uint8_t *rd, int rn); /* write-then-read; 1 ok */
int  hal_exp_spi(const uint8_t *tx, uint8_t *rx, int n);   /* full-duplex (tx/rx may be NULL); 1 ok        */
void hal_exp_spi_cs(int level);                            /* drive the SPI chip-select (PG8), 0/1         */
int  hal_exp_uart_write(const uint8_t *b, int n);          /* bytes written                                */
int  hal_exp_uart_read(uint8_t *b, int max);               /* bytes read (0..max)                          */
void hal_exp_gpio_set(int idx, int level);                 /* drives idx (0=PE13, 1=PA15) as an output     */
int  hal_exp_gpio_get(int idx);                            /* reads idx                                    */

/* ---- sensors / peripherals ------------------------------------------------------ */
typedef struct { float gx, gy, gz; float ax, ay, az; } imu_sample_t;   /* rad/s, m/s^2 */
int  hal_imu_read(imu_sample_t *s);
typedef struct { int valid; double lat, lon; float alt_m; float hdop; uint32_t utc_s; int sats; } gnss_fix_t;
int  hal_gnss_read(gnss_fix_t *fix);
float hal_battery_v(void);
int   hal_battery_pct(void);
int   hal_charging(void);
float hal_rail_v(int rail);                /* 0 VSYS 1 +3V3 2 +5VA 3 -5VA 4 +12V 5 VTX 6 VBRIDGE */
float hal_temp_c(void);

/* ---- storage -------------------------------------------------------------------- */
int  hal_nvm_read(void *buf, size_t len);          /* settings block in MCU flash             */
int  hal_nvm_write(const void *buf, size_t len);
int  hal_coil_eeprom_read(uint8_t buf[128]);       /* DS2431 in the coil, 1-Wire; 0 = no coil */
int  hal_coil_eeprom_write(const uint8_t buf[128]);
int  hal_sd_append(const char *path, const char *line);   /* 0 ok, <0 no card             */
int  hal_sd_present(void);

/* ---- time / power --------------------------------------------------------------- */
uint32_t hal_millis(void);
void hal_delay_ms(uint32_t ms);
void hal_power_off(void);
void hal_analog_enable(int on);            /* TPS65131 / LT3757 enables                     */
void hal_hv_enable(int on);                /* 100 V boost                                   */
void hal_hv_bleed(int on);
void hal_log(const char *fmt, ...);        /* debug console                                 */

#endif

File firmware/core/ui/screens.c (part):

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    gfx_text(fb, 16, 18, &FONT_BOLD, "DIAGNOSTICS", 1);
    int y = 40;
    snprintf(b, sizeof b, "FW %s   uptime %lus   %.1f C", MDX_FW_VERSION, (unsigned long)st->uptime_s, st->temp_c); gfx_text(fb, 16, y, &FONT_SMALL, b, 1); y += 12;
    snprintf(b, sizeof b, "Rails VSYS %.2f  3V3 %.2f  5VA %.2f  -5VA %.2f  12V %.1f", hal_rail_v(0), hal_rail_v(1), hal_rail_v(2), hal_rail_v(3), hal_rail_v(4)); gfx_text(fb, 16, y, &FONT_SMALL, b, 1); y += 12;
    snprintf(b, sizeof b, "VTX %.1f V   VBRIDGE %.1f V   ITX %.3f A rms   fault %d", st->vtx_v, st->vbridge_v, st->itx_rms_a, st->tx_fault); gfx_text(fb, 16, y, &FONT_SMALL, b, 1); y += 12;
    snprintf(b, sizeof b, "Coil %s  chip %d  L %.3f mH  R %.2f  cal %d", d->coil.cal.name, d->coil.has_chip, d->coil.cal.L_tx_mH, d->coil.cal.R_tx_ohm, d->coil.calibrated); gfx_text(fb, 16, y, &FONT_SMALL, b, 1); y += 12;
    snprintf(b, sizeof b, "Period M %d  lines %.2f %.2f %.2f %.2f %.2f kHz", d->demod.M, d->demod.f_hz[0] / 1e3f, d->demod.f_hz[1] / 1e3f, d->demod.f_hz[2] / 1e3f, d->demod.f_hz[3] / 1e3f, d->demod.f_hz[4] / 1e3f); gfx_text(fb, 16, y, &FONT_SMALL, b, 1); y += 12;
    snprintf(b, sizeof b, "Floor %.1f uohm  thresh %.1f uohm  noise %.1f uohm", d->noise_floor * 1e6f, d->thresh * 1e6f, st->noise_level * 1e6f); gfx_text(fb, 16, y, &FONT_SMALL, b, 1); y += 12;
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        const item_t *it = &MENU[u->menu_idx];
        if (u->editing) {
            if (pressed & (KEY_LEFT | KEY_RIGHT)) { int v = it->get(d) + ((pressed & KEY_RIGHT) ? 1 : -1); if (v < it->lo) v = it->hi; if (v > it->hi) v = it->lo; it->set(d, v); detector_apply_settings(d); }
            if (pressed & (KEY_BACK | KEY_MENU)) u->editing = 0;
        } else {
            if (pressed & KEY_UP) u->menu_idx = (u->menu_idx + NMENU - 1) % NMENU;
            if (pressed & KEY_DOWN) u->menu_idx = (u->menu_idx + 1) % NMENU;
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        }
        break; }
    case SCR_LOG:
        if (pressed & KEY_RIGHT) u->mark_find = 1;
        if (pressed & KEY_BACK) u->screen = SCR_MENU;
        break;
    case SCR_COIL_WIZARD:
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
